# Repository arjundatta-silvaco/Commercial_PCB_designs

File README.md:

# Commercial PCB designs

A repository with circuits schematics and PCB designs of breakout boards.

Check out my blog: [https://semicon.world/](https://semicon.world/)

Support the blog and the GitHub: [https://razorpay.me/@semiconworld](https://razorpay.me/@semiconworld)

### License Notice: This repository is provided for personal study and educational reference. Research publication, commercial use, redistribution, and reuse of repository contents require prior permission. See the LICENSE file for details.

#### Currently in the Repository:

* LM2596S-adj Buck converter 9-12.9V to 5V 3A: Complete
* TP5100 Battery Charger 2S: Only Circuit
* HX-2S-JH20: Only Circuit
* HUSB238 USB-C Power Delivery: Planned
* ESP-32 DEVKIT V1 WROOM-32: Planned

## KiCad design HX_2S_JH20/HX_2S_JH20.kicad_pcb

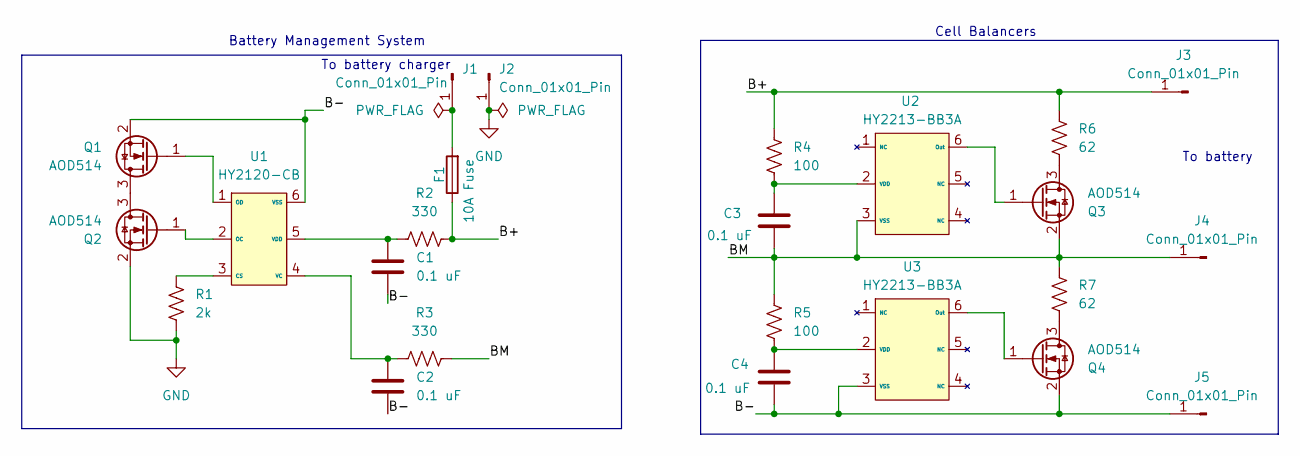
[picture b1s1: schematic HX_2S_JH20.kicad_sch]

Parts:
C1, C2, C3, C4: 0.1 uF; C_0603_1608Metric; Part number GRM188R61E104KA01D
F1: 10A Fuse; Fuse_0603_1608Metric; Part number 0685H9100-01
J1, J2, J3, J4, J5: Conn_01x01_Pin; SolderWire-4sqmm_1x01_D3mm_OD6mm; Part number Bare pad
Q1, Q2, Q3, Q4: AOD514; TO-252-2; Part number AOD514
R1: 2k; R_0603_1608Metric; Part number ERJ-3EKF2001V
R2, R3: 330; R_0603_1608Metric; Part number ERJ-3GEYJ331V
R4, R5: 100; R_0603_1608Metric; Part number ESR03EZPF1000
R6, R7: 62; R_2512_6332Metric; Part number ERJ-1TYJ620U
U1: HY2120-CB; SOT-23-6; Part number HY2120-CB
U2, U3: HY2213-BB3A; SOT-23-6; Part number HY2213-BB3A

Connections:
/B+: F1.1, J3.1 (Pin_1_1), R2.2, R4.1, R6.1
/B-: C1.2, C2.2, C4.2, J5.1 (Pin_1_1), Q1.2 (S), Q4.2 (S), U1.6 (VSS), U3.3 (VSS)
/BM: C3.2, J4.1 (Pin_1_1), Q3.2 (S), R3.2, R5.1, R7.1, U2.3 (VSS)
GND: J2.1 (Pin_1_1), Q2.2 (S), R1.2
unnamed: F1.2, J1.1 (Pin_1_1)
unnamed: Q1.3 (D), Q2.3 (D)
unnamed: Q1.1 (G), U1.1 (OD)
unnamed: Q2.1 (G), U1.2 (OC)
unnamed: Q3.3 (D), R6.2
unnamed: Q3.1 (G), U2.6 (Out)
unnamed: Q4.3 (D), R7.2
unnamed: Q4.1 (G), U3.6 (Out)
unnamed: R1.1, U1.3 (CS)
unnamed: C2.1, R3.1, U1.4 (VC)
unnamed: C1.1, R2.1, U1.5 (VDD)
unnamed: C3.1, R4.2, U2.2 (VDD)
unnamed: C4.1, R5.2, U3.2 (VDD)

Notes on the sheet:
To battery
Battery Management System
To battery charger
Cell Balancers

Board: 2 copper layers, 24 parts (0 on the bottom side), 17 nets, no tracks yet.

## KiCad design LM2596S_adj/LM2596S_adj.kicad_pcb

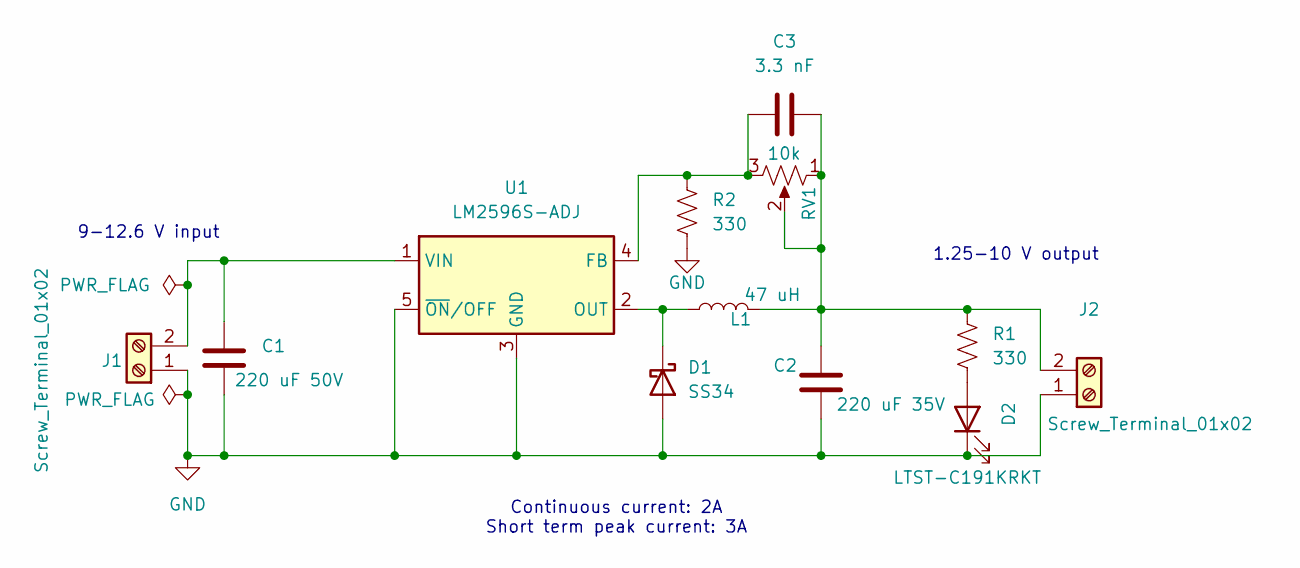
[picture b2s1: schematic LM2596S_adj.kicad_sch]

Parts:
C1: 220 uF 50V; CAP_EEHZS1H221P; Part number EEH-ZS1H221P
C2: 220 uF 35V; CAP_EEEFK1V221P; Part number EEE-FK1V221P
C3: 3.3 nF; C_0603_1608Metric; Part number 0603B332K101SD
D1: SS34; D_SMA; Part number SS34
D2: LTST-C191KRKT; LED_0603_1608Metric; Part number LTST-C191KRKT
J1, J2: Screw_Terminal_01x02; TerminalBlock_RND_205-00001_1x02_P5.00mm_Horizontal; Part number 691137710002
L1: 47 uH; L_Wuerth_WE-PD-Typ-LS; Part number 7447709470
R1, R2: 330; R_0603_1608Metric; Part number RC0603FR-07330RL
RV1: 10k; TRIM_3296W-1-103; Part number 3296W-1-103
U1: LM2596S-ADJ; TO-263-5_TabPin3; Part number LM2596S-ADJ

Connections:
GND: C1.2, C2.2, D1.2 (A), D2.1 (K), J1.1, J2.1, R2.2, U1.3 (GND), U1.5 (~ON/OFF)
unnamed: D1.1 (K), L1.1, U1.2 (OUT)
unnamed: D2.2 (A), R1.2
unnamed: C1.1, J1.2, U1.1 (VIN)
unnamed: C2.1, C3.2, J2.2, L1.2, R1.1, RV1.1, RV1.2
unnamed: C3.1, R2.1, RV1.3, U1.4 (FB)

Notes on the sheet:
1.25-10 V output
9-12.6 V input
Continuous current: 2A Short term peak current: 3A

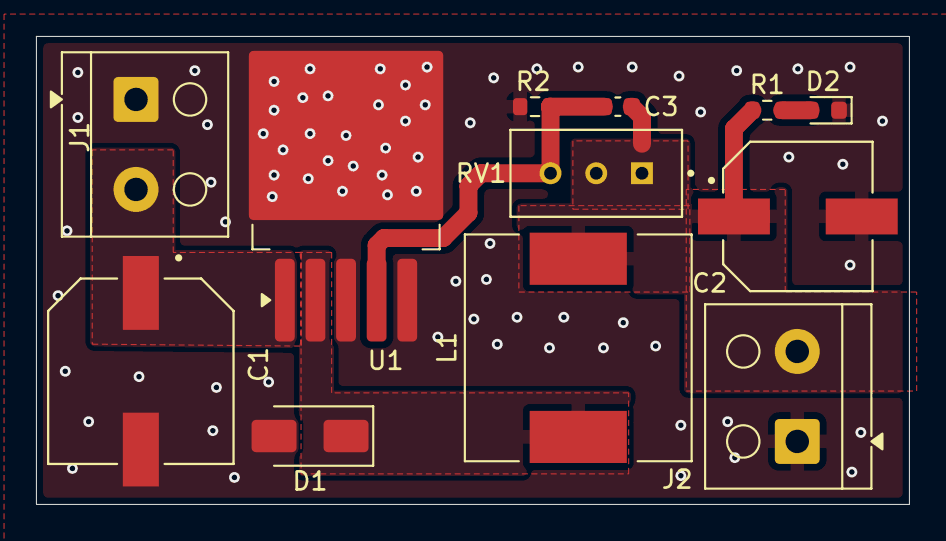
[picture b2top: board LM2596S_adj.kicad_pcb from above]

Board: 2 copper layers, 48.5 x 26.0 mm, 12 parts (0 on the bottom side), 6 nets.
